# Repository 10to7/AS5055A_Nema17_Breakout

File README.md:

Nema 17 breakout for AS5055A
==================

**Warning** _currently untested, may contain errors._

Hall effect position sensor breakout board with a nema 17 footprint and mounting holes.

Contains a level shifter for operation at 5V.

| Top | Bottom |
|---|---|
|![PCBfront]|![PCBback]|

[PCBfront]: front.png "PCB front"
[PCBback]: back.png "PCB Back"

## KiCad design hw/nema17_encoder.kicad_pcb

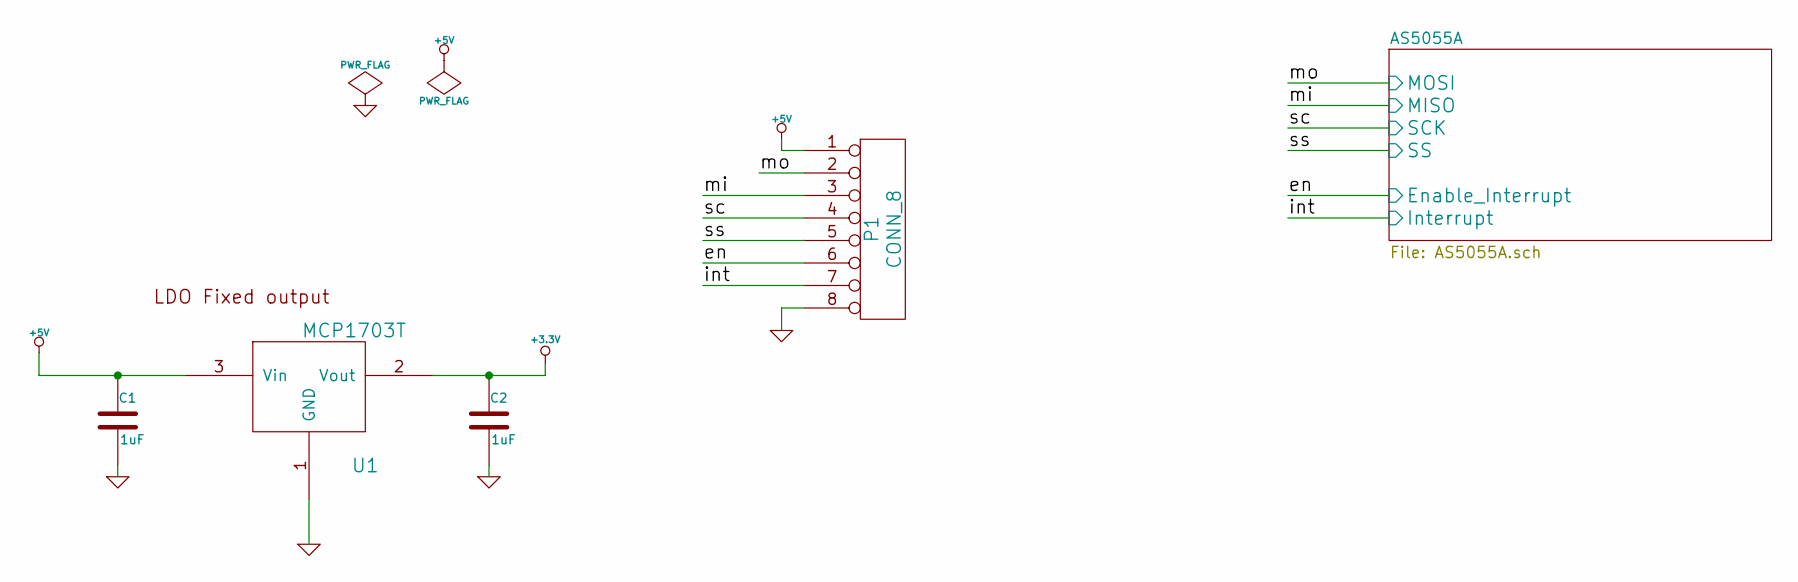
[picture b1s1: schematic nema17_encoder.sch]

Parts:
C1, C2: 1uF
P1: CONN_8
U1: MCP1703T

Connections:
+3.3V: C2.1, U1.2 (Vout); also elsewhere on the board
+5V: C1.1, P1.1, U1.3 (Vin); also elsewhere on the board
/AS5055A/Enable_Interrupt: P1.6; also elsewhere on the board
/AS5055A/Interrupt: P1.7; also elsewhere on the board
/AS5055A/MISO: P1.3; also elsewhere on the board
/AS5055A/MOSI: P1.2; also elsewhere on the board
/AS5055A/SCK: P1.4; also elsewhere on the board
/AS5055A/SS: P1.5; also elsewhere on the board
GND: C1.2, C2.2, P1.8, U1.1 (GND); also elsewhere on the board

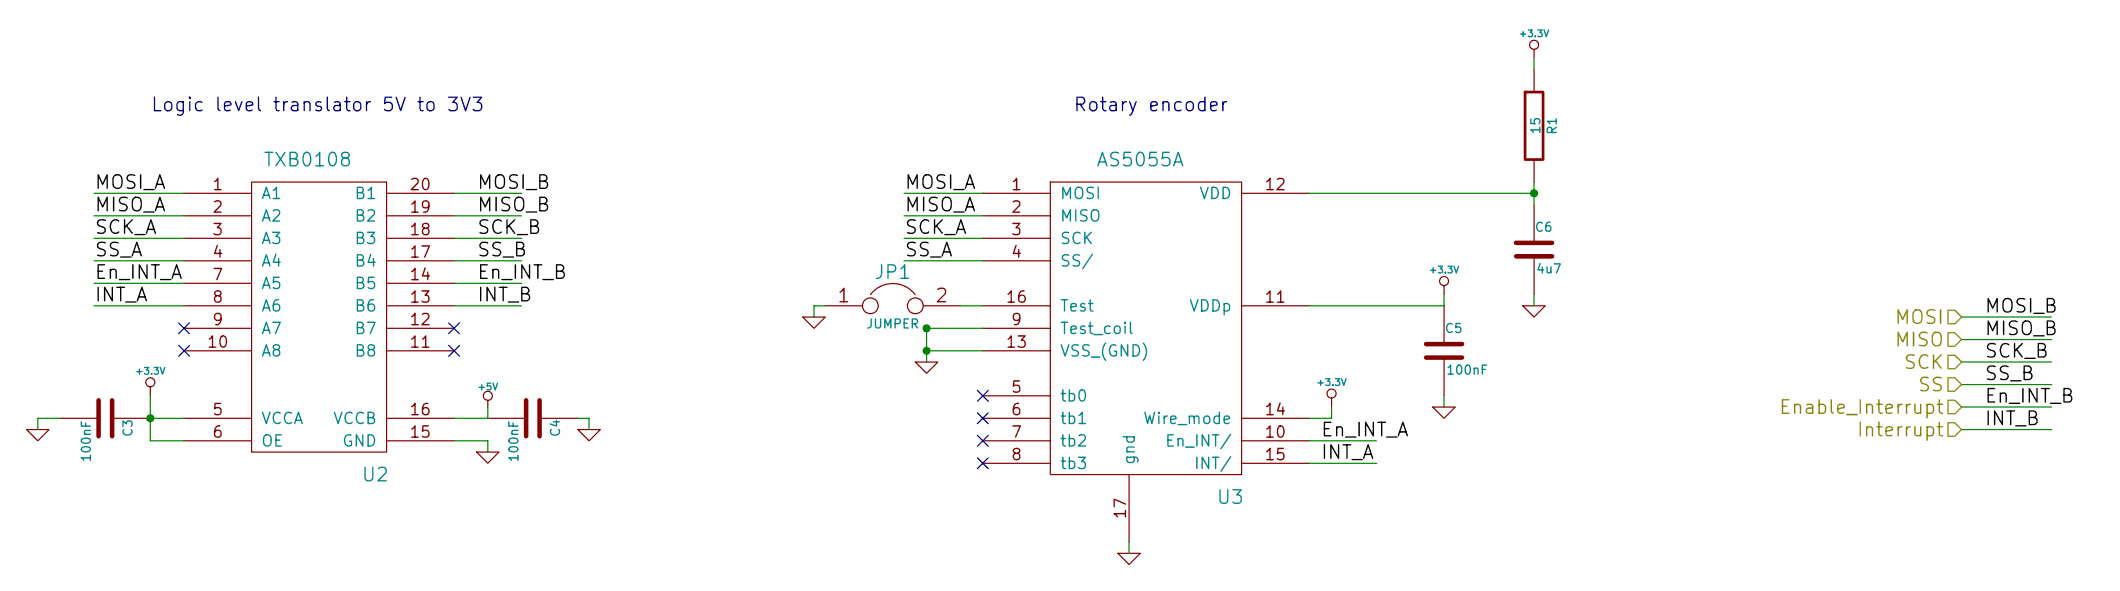
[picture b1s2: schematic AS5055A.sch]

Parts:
C3, C4, C5: 100nF
C6: 4u7
JP1: JUMPER
R1: 15
U2: TXB0108
U3: AS5055A

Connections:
+3.3V: C3.1, C5.1, R1.1, U2.5 (VCCA), U2.6 (OE), U3.11 (VDDp), U3.14 (Wire_mode); also elsewhere on the board
+5V: C4.2, U2.16 (VCCB); also elsewhere on the board
/AS5055A/En_INT_A: U2.7 (A5), U3.10 (En_INT/)
/AS5055A/Enable_Interrupt: U2.14 (B5); also elsewhere on the board
/AS5055A/INT_A: U2.8 (A6), U3.15 (INT/)
/AS5055A/Interrupt: U2.13 (B6); also elsewhere on the board
/AS5055A/MISO: U2.19 (B2); also elsewhere on the board
/AS5055A/MISO_A: U2.2 (A2), U3.2 (MISO)
/AS5055A/MOSI: U2.20 (B1); also elsewhere on the board
/AS5055A/MOSI_A: U2.1 (A1), U3.1 (MOSI)
/AS5055A/SCK: U2.18 (B3); also elsewhere on the board
/AS5055A/SCK_A: U2.3 (A3), U3.3 (SCK)
/AS5055A/SS: U2.17 (B4); also elsewhere on the board
/AS5055A/SS_A: U2.4 (A4), U3.4 (SS/)
GND: C3.2, C4.1, C5.2, C6.2, JP1.1, U2.15 (GND), U3.9 (Test_coil), U3.13 (VSS_(GND)), U3.17 (gnd); also elsewhere on the board
unnamed: C6.1, R1.2, U3.12 (VDD)
unnamed: JP1.2, U3.16 (Test)

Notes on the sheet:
Logic level translator 5V to 3V3
Rotary encoder

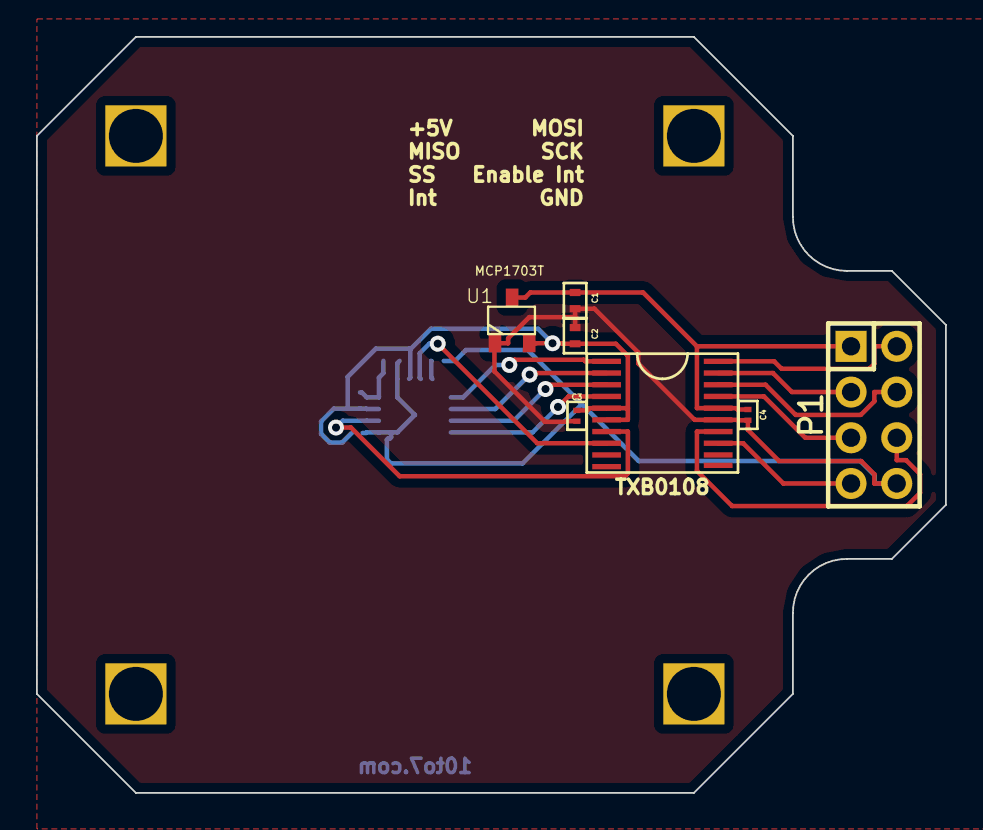
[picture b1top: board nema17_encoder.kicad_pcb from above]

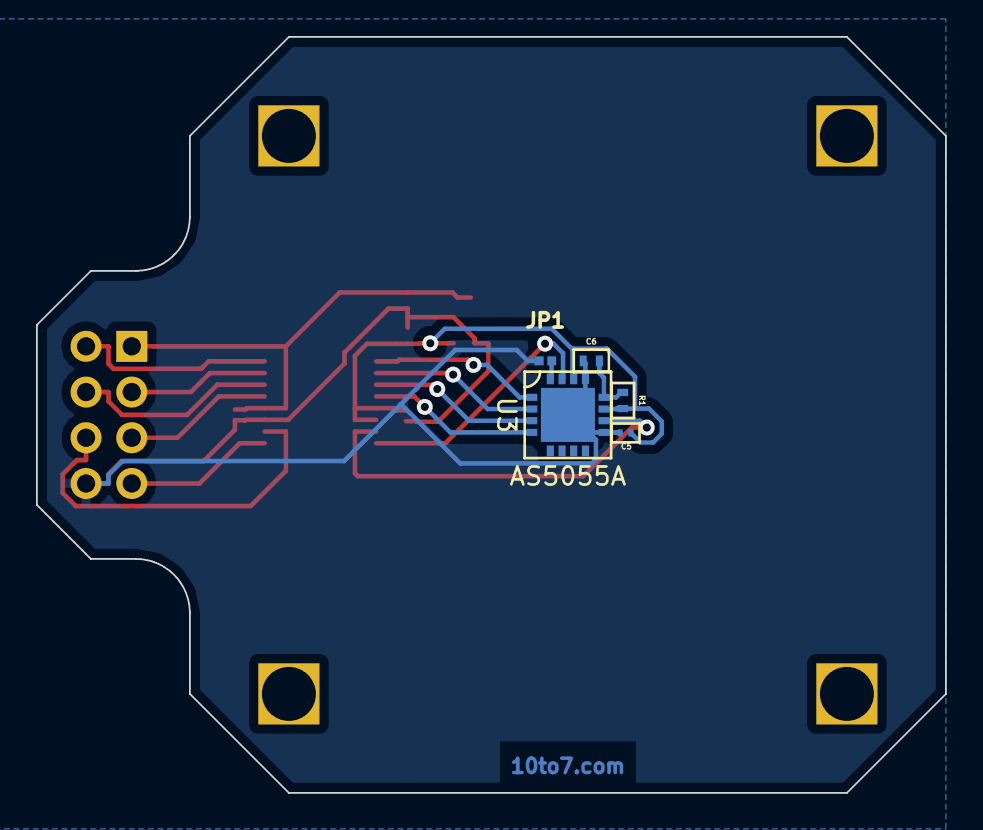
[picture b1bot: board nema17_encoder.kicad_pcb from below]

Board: 2 copper layers, 50.5 x 42.0 mm, 16 parts (5 on the bottom side), 17 nets.

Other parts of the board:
3mmHole, 3mmHole#2, 3mmHole#3, 3mmHole#4: VAL**; 3mmHole

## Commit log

2014-07-03 Added the board rendering to the project
2014-07-12 Added an example of using the AS5055 chip found on the arduino forums
2014-07-13 Added some documentation so it is in one place. This information can be 'freely' found around the web.
2014-07-13 Added header file to go with the C
2014-07-15 added missed save
